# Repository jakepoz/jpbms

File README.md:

**JPBms**

JPBms is a simple BMS for solar charging and balancing a 3-cell lithium ion battery.

The key thing about it is that it uses no custom ICs, beyond a basic microcontroller. 
That is to say that it depends on no hard-to-find custom ICs that will be obsolete 3 years from now.
It implements a basic charging circuit that can charge a ~12V 3S battery from basically any input power source between
6V-24V, including if that source is a solar panel.

-------------------------------

[v1.3 Schematics](JPBms2-v1.3.pdf)

-----------------------------
- STM32L053 microcontroller
- It's just an inductor with a full set of switches on it, so you can customize it
- Simple resistive balancing
- Single layer board design for easy JLCPCB style production
  - ~$150 to order 5 from JLCPCB, way cheaper in bulk
- Low ~100uA quiescent current
- XT30 solar panel connector, JST-XH battery balance connector

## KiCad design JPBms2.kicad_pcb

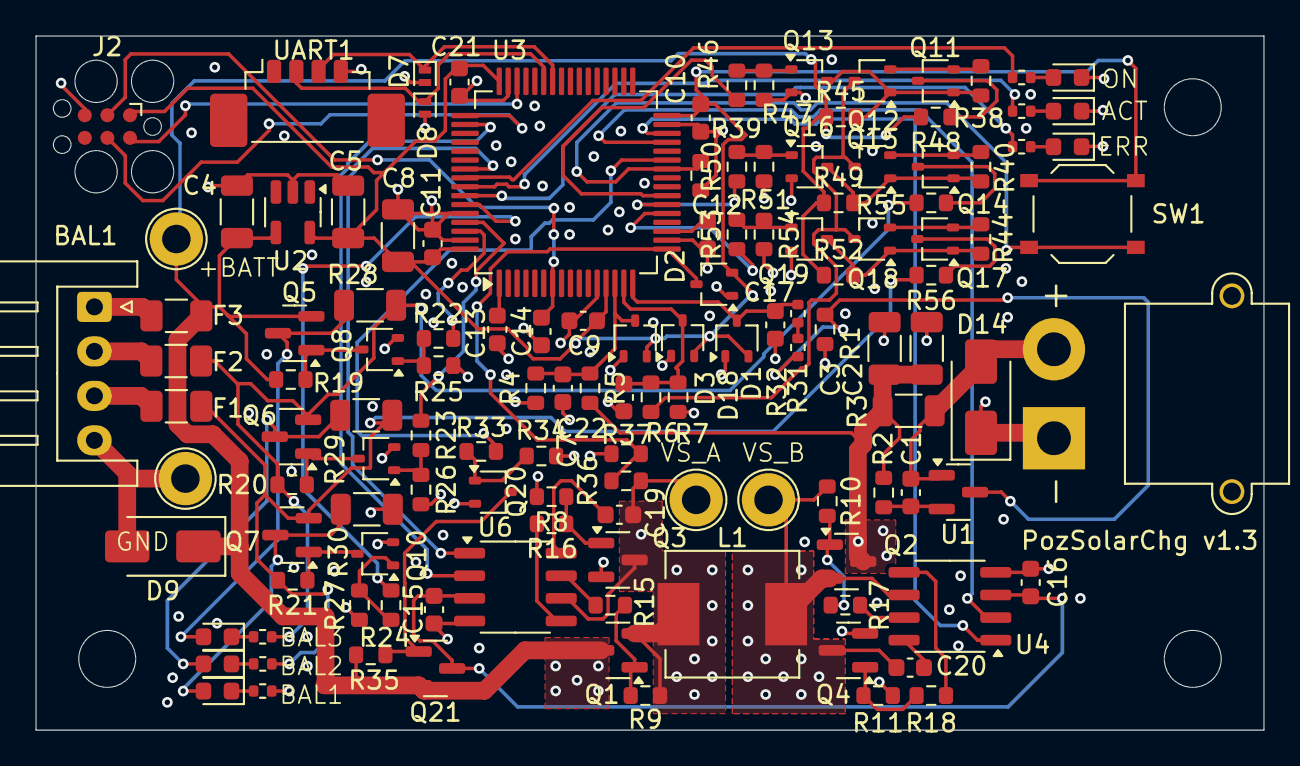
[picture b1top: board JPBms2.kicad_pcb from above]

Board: 4 copper layers, 69.0 x 39.0 mm, 132 parts (0 on the bottom side), 81 nets.

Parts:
BAL1: Conn_01x04 JST-XH; JST_XH_S4B-XH-A_1x04_P2.50mm_Horizontal_Tight
C1: 10p; C_0603_1608Metric
C2, C3, C4, C8: 10u; C_1206_3216Metric
C5: 47u; C_1206_3216Metric
C7, C9, C10, C11, C12, C13, C14, C17, C21, C22: .1u; C_0603_1608Metric
C15, C16, C19, C20: 1u; C_0603_1608Metric
D1, D2, D3, D18: BAT54SW; SOT-323_SC-70
D4: LED_G; LED_0603_1608Metric
D5, D11, D12, D13: LED_Y; LED_0603_1608Metric
D6: LED_R; LED_0603_1608Metric
D7, D8: H5VL10B; D_SOD-882
D9: SMAJ16A; D_SMA
D14: SMAJ30CA; D_SMA
F1, F2, F3: 30V 750mA; Fuse_1206_3216Metric
H1, H2, H3: MountingHole; MountingHole_3.2mm_M3
J1: XT30PW-M; AMASS_XT30PW-M_1x02_P2.50mm_Horizontal
J2: Conn_ARM_SWD_TagConnect_TC2030; Tag-Connect_TC2030-IDC-FP_2x03_P1.27mm_Vertical
L1: 47uH; L_Sunlord_MWSA0605S
Q1, Q2, Q3, Q4: AO3400A; SOT-23
Q5, Q6, Q7, Q21: AO3401A; SOT-23
Q8, Q9, Q10, Q13, Q16, Q19, Q20: 2N7002; SOT-323_SC-70
Q11, Q12, Q14, Q15, Q17, Q18: SK2301AW; SOT-323_SC-70
R1: 3k; R_0603_1608Metric
R2, R37: 4.7k; R_0603_1608Metric
R3: 0.1; R_1206_3216Metric
R4: 2k; R_0603_1608Metric
R5: 18k; R_0603_1608Metric
R6: 7500; R_0603_1608Metric
R7: 1600; R_0603_1608Metric
R8, R9, R10, R11, R19, R20, R21, R25, R26, R27, R34, R35, R38, R40, R44, R45, R47, R49, R51, R52, R54: 1M; R_0603_1608Metric
R12, R13, R14, R31, R32, R41, R42, R43: 150; R_0402_1005Metric
R15, R16, R17, R18, R48, R55, R56: 75; R_0603_1608Metric
R22, R23, R24, R33, R46, R50, R53: 1k; R_0603_1608Metric
R28, R29, R30: 100; R_1206_3216Metric
R36: 56k; R_0603_1608Metric
R39: 10M; R_0603_1608Metric
SW1: SW_Push; SW_Push_1P1T_XKB_TS-1187A
TP1: GND; TestPoint_Loop_D2.60mm_Drill1.6mm_Beaded
TP2: +BATT; TestPoint_Loop_D2.60mm_Drill1.6mm_Beaded
TP5, TP6: TestPoint; TestPoint_Loop_D2.60mm_Drill1.6mm_Beaded
U1: ZXCT1107; SOT-23
U2: ST715M25R; SOT-23-5
U3: STM32L053R8Tx; LQFP-64_10x10mm_P0.5mm
U4, U6: L6388E; SO-8_3.9x4.9mm_P1.27mm
UART1: Conn_01x04 Picoblade; Molex_PicoBlade_53398-0471_1x04-1MP_P1.25mm_Vertical

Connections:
+BATT: C4.1, D9.1 (A1), F3.2, Q1.3 (D), Q5.2 (S), Q21.2 (S), R19.1, R35.1, R45.1, R48.2, R49.1, R52.1, TP2.1, U2.4 (Vin)
/BuckBoost/DRIVER_VCC: C15.2, C16.2, Q21.3 (D), U4.3 (VCC), U6.3 (VCC)
/BuckBoost/GATE_BOT_A: Q3.1 (G), R8.1, R16.2
/BuckBoost/GATE_BOT_B: Q4.1 (G), R11.1, R18.2
/BuckBoost/GATE_TOP_A: Q1.1 (G), R9.1, R15.2
/BuckBoost/GATE_TOP_B: Q2.1 (G), R10.1, R17.2
/BuckBoost/VS_A: C19.1, L1.1, Q1.2 (S), Q3.3 (D), R9.2, R36.1, TP5.1, U6.6 (OUT)
/BuckBoost/VS_B: C20.1, L1.2, Q2.2 (S), Q4.3 (D), R10.2, TP6.1, U4.6 (OUT)
/MCU/LED_ACTIVE: R13.1, U3.57 (TIM22_CH2)
/MCU/LED_ERROR: R14.1, U3.58 (PB6)
/MCU/LED_ON: R12.1, U3.56 (TIM22_CH1)
/MCU/NRST: C14.1, J2.3 (~RESET), U3.7 (NRST)
/MCU/SWCLK: J2.4 (SWCLK), U3.49 (SYS_SWCLK)
/MCU/SWDIO: J2.2 (SWDIO), U3.46 (SYS_SWDIO)
/MCU/SWITCH: R39.2, SW1.1, U3.26 (PB0)
/MCU/USART1_RX: D8.1 (A1), U3.43 (USART1_RX), UART1.2
/MCU/USART1_TX: D7.1 (A1), U3.42 (USART1_TX), UART1.3
/Power/Vs+: C1.1, D14.2 (A2), J1.2, R3.2, U1.1 (Vs+)
CELL4V_ADC_EN: R53.1, U3.21 (PA5)
CELL8V_ADC_EN: R50.1, U3.22 (PA6)
CELL_4V: F1.2, Q7.2 (S), R21.1, R29.2, R42.1, R56.2
CELL_8V: F2.2, Q6.2 (S), R20.1, R28.2, R41.1, R55.2
COMP2_INP: D2.3 (COM), R36.2, R37.1, U3.17 (COMP2_INP)
DD_BOT_A: U3.55 (TIM2_CH2), U6.1 (LIN)
DD_BOT_B: U3.30 (TIM2_CH4), U4.1 (LIN)
DD_TOP_A: U3.50 (TIM2_CH1), U6.2 (HIN)
DD_TOP_B: U3.29 (TIM2_CH3), U4.2 (HIN)
DRIVERS_EN: R33.1, U3.27 (PB1)
GND: BAL1.4, C2.1, C3.1, C4.2, C5.2, C7.2, C8.2, C9.2, C10.2, C11.2, C12.2, C13.2, C14.2, C15.1, C16.1, C17.1, C21.2, C22.2, D1.1 (A), D2.1 (A), D3.1 (A), D4.1 (K), D5.1 (K), D6.1 (K), D7.2 (A2), D8.2 (A2), D9.2 (A2), D14.1 (A1), D18.1 (A), J1.1, J2.5 (GND), Q3.2 (S), Q4.2 (S), Q8.2 (S), Q9.2 (S), Q10.2 (S), Q13.2 (S), Q16.2 (S), Q19.2 (S), Q20.2 (S), R1.2, R4.1, R7.1, R8.2, R11.2, R25.2, R26.2, R27.2, R30.2, R34.2, R37.2, R39.1, R43.1, R47.2, R51.2, R54.2, TP1.1, U2.2 (GND), U3.12 (VSSA), U3.18 (VSS), U3.31 (VSS), U3.47 (VSS), U3.60 (BOOT0), U3.63 (VSS), U4.4 (GND), U6.4 (GND), UART1.4
NBAL_1: R24.1, U3.59 (PB7)
NBAL_2: R23.1, U3.61 (PB8)
NBAL_3: R22.1, U3.62 (PB9)
unnamed: BAL1.1, F3.1
unnamed: BAL1.2, F2.1
unnamed: BAL1.3, F1.1
unnamed: D4.2 (A), R12.2
unnamed: D5.2 (A), R13.2
unnamed: D6.2 (A), R14.2
unnamed: D11.2 (A), Q5.3 (D), R28.1
unnamed: D11.1 (K), R41.2
unnamed: D12.2 (A), Q6.3 (D), R29.1
unnamed: D12.1 (K), R42.2
unnamed: D13.2 (A), Q7.3 (D), R30.1
unnamed: D13.1 (K), R43.2
unnamed: Q5.1 (G), Q8.3 (D), R19.2
unnamed: Q6.1 (G), Q9.3 (D), R20.2
unnamed: Q8.1 (G), R22.2, R25.1
unnamed: Q9.1 (G), R23.2, R26.1
unnamed: Q7.1 (G), Q10.3 (D), R21.2
unnamed: Q10.1 (G), R24.2, R27.1
unnamed: Q11.3 (D), R48.1
unnamed: Q11.1 (G), Q12.1 (G), Q13.3 (D), R38.1, R45.2
unnamed: Q11.2 (S), Q12.2 (S), R38.2
unnamed: Q12.3 (D), Q15.3 (D), Q18.3 (D), R6.1
unnamed: Q13.1 (G), R46.2, R47.1
unnamed: Q14.3 (D), R55.1
unnamed: Q14.1 (G), Q15.1 (G), Q16.3 (D), R40.1, R49.2
unnamed: Q14.2 (S), Q15.2 (S), R40.2
unnamed: Q16.1 (G), R50.2, R51.1
unnamed: Q17.3 (D), R56.1
unnamed: Q17.1 (G), Q18.1 (G), Q19.3 (D), R44.1, R52.2
unnamed: Q17.2 (S), Q18.2 (S), R44.2
unnamed: Q19.1 (G), R53.2, R54.1
unnamed: Q20.3 (D), Q21.1 (G), R35.2
unnamed: Q20.1 (G), R33.2, R34.1
unnamed: R31.2, R32.1
unnamed: R1.1, R31.1, U1.3 (OUT)
unnamed: C1.2, R2.2, U1.2 (Vs-)
unnamed: C13.1, U3.1 (VLCD)
unnamed: R17.1, U4.7 (HVG)
unnamed: R18.1, U4.5 (LVG)
unnamed: C20.2, U4.8 (VBOOT)
unnamed: R15.1, U6.7 (HVG)
unnamed: R16.1, U6.5 (LVG)
unnamed: C19.2, U6.8 (VBOOT)
SOLAR_CURRENT_ADC: C17.2, D1.3 (COM), R32.2, U3.16 (ADC_IN2)
VBATT_ADC: C22.1, D18.3 (COM), R6.2, R7.2, U3.15 (ADC_IN1)
VBATT_ADC_EN: R46.1, U3.23 (PA7)
VDD: C5.1, C8.1, C9.1, C10.1, C11.1, C12.1, C21.1, D1.2 (K), D2.2 (K), D3.2 (K), D18.2 (K), J2.1 (VCC), SW1.2, U2.5 (Vout), U3.13 (VDDA), U3.19 (VDD), U3.32 (VDD), U3.48 (VDD_USB), U3.64 (VDD)
VSOLAR: C2.2, C3.2, Q2.3 (D), R2.1, R3.1, R5.2
VSOLAR_ADC: C7.1, D3.3 (COM), R4.2, R5.1, U3.14 (ADC_IN0)

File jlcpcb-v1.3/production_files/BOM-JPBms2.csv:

Comment,Designator,Footprint,LCSC
LED_G,D4,LED_0603_1608Metric,C12624
10u,"C2,C3,C4,C8",C_1206_3216Metric,C13585
.1u,"C10,C11,C12,C13,C14,C17,C21,C22,C7,C9",C_0603_1608Metric,C14663
AO3401A,"Q21,Q5,Q6,Q7",SOT-23,C15127
Conn_01x04 JST-XH,BAL1,JST_XH_S4B-XH-A_1x04_P2.50mm_Horizontal_Tight,C157925
1u,"C15,C16,C19,C20",C_0603_1608Metric,C15849
10p,C1,C_0603_1608Metric,C1634
100,"R28,R29,R30",R_1206_3216Metric,C17901
AO3400A,"Q1,Q2,Q3,Q4",SOT-23,C20917
1k,"R22,R23,R24,R33,R46,R50,R53",R_0603_1608Metric,C21190
LED_R,D6,LED_0603_1608Metric,C2286
LED_Y,"D11,D12,D13,D5",LED_0603_1608Metric,C2287
1M,"R10,R11,R19,R20,R21,R25,R26,R27,R34,R35,R38,R40,R44,R45,R47,R49,R51,R52,R54,R8,R9",R_0603_1608Metric,C22935
2k,R4,R_0603_1608Metric,C22975
4.7k,"R2,R37",R_0603_1608Metric,C23162
56k,R36,R_0603_1608Metric,C23206
Conn_01x04 Picoblade,UART1,Molex_PicoBlade_53398-0471_1x04-1MP_P1.25mm_Vertical,C234195
L6388E,"U4,U6",SO-8_3.9x4.9mm_P1.27mm,C23921
150,"R12,R13,R14,R31,R32,R41,R42,R43",R_0402_1005Metric,C25082
18k,R5,R_0603_1608Metric,C25810
10M,R39,R_0603_1608Metric,C26097
ST715M25R,U2,SOT-23-5,C2832805
0.1,R3,R_1206_3216Metric,C2903496
SW_Push,SW1,SW_Push_1P1T_XKB_TS-1187A,C318884
47uH,L1,L_Sunlord_MWSA0605S,C408471
3k,R1,R_0603_1608Metric,C4211
75,"R15,R16,R17,R18,R48,R55,R56",R_0603_1608Metric,C4275
XT30PW-M,J1,AMASS_XT30PW-M_1x02_P2.50mm_Horizontal,C431092
SMAJ30CA,D14,D_SMA,C5249596
7500,R6,R_0603_1608Metric,C728597
2N7002,"Q10,Q13,Q16,Q19,Q20,Q8,Q9",SOT-323_SC-70,C7420322
H5VL10B,"D7,D8",D_SOD-882,C7420372
STM32L053R8Tx,U3,LQFP-64_10x10mm_P0.5mm,C784738
BAT54SW,"D1,D18,D2,D3",SOT-323_SC-70,C78606
ZXCT1107,U1,SOT-23,C82766
1600,R7,R_0603_1608Metric,C861205
47u,C5,C_1206_3216Metric,C96123
SK2301AW,"Q11,Q12,Q14,Q15,Q17,Q18",SOT-323_SC-70,C962722
30V 750mA,"F1,F2,F3",Fuse_1206_3216Metric,C976305
+BATT,TP2,TestPoint_Loop_D2.60mm_Drill1.6mm_Beaded,
TestPoint,TP6,TestPoint_Loop_D2.60mm_Drill1.6mm_Beaded,
GND,TP1,TestPoint_Loop_D2.60mm_Drill1.6mm_Beaded,
TestPoint,TP5,TestPoint_Loop_D2.60mm_Drill1.6mm_Beaded,
SMAJ16A,D9,D_SMA,

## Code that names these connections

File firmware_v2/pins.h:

#ifndef PINS_H
#define PINS_H

#define USART1_PORT GPIOA
#define USART1_TX_PIN GPIO9
#define USART1_RX_PIN GPIO10

#define BALANCE_PORT GPIOB
#define BALANCE_1_PIN GPIO7
#define BALANCE_2_PIN GPIO8
#define BALANCE_3_PIN GPIO9

#define LED_ON_PORT GPIOB
#define LED_ON_PIN GPIO4

#define LED_ACTIVE_PORT GPIOB
#define LED_ACTIVE_PIN GPIO5

#define LED_ERROR_PORT GPIOB
#define LED_ERROR_PIN GPIO6

#define VSOLAR_ADC_PORT GPIOA
#define VSOLAR_ADC_PIN GPIO0
#define VSOLAR_ADC_CH 0

#define VBATT_ADC_PORT GPIOA
#define VBATT_ADC_PIN GPIO1
#define VBATT_ADC_CH 1

#define SOLAR_CURRENT_ADC_PORT GPIOA
#define SOLAR_CURRENT_ADC_PIN GPIO2
#define SOLAR_CURRENT_ADC_CH 2

#define TEMP_SENSOR_ADC_CH 18
#define VREFINT_ADC_CH 17

#define ADC_MULTIPLEX_PORT GPIOA
#define ADC_MULTIPLEX_CELL4V_PIN GPIO5
#define ADC_MULTIPLEX_CELL8V_PIN GPIO6
#define ADC_MULTIPLEX_VBATT_PIN GPIO7

#define SWITCH_PORT GPIOB
#define SWITCH_PIN GPIO0

#define DRIVERS_EN_PORT GPIOB
#define DRIVERS_EN_PIN GPIO1

#define BB_SW_A_PORT GPIOA
#define BB_SW_A_PIN GPIO15

#define BB_D_A_PORT GPIOB
#define BB_D_A_PIN GPIO3

#define BB_SW_B_PORT GPIOB
#define BB_SW_B_PIN GPIO10

#define BB_D_B_PORT GPIOB
#define BB_D_B_PIN GPIO11


#endif

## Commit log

2024-04-18 Many stages done
2024-04-18 prefs
2024-04-18 removing old
2024-04-18 Some part selections
2024-04-19 Text
2024-04-20 Connect adc
2024-04-21 Starting to do layout
2024-04-24 Adding simple balance circuits
2024-04-26 Footprint
2024-04-26 Smaller diodes, more work
2024-04-26 Some more placement
2024-04-26 More layout adust
2024-04-26 Smallfixups
2024-04-27 Routing more
2024-04-27 Routing
2024-05-03 Layout done
2024-05-03 bom pt1
2024-05-06 Assigning PNs
2024-05-06 slight changes
2024-05-06 sent to jlcpcb
2024-05-14 Schematics updated P mosfets
2024-05-14 New design and layout
2024-05-15 Finishing layout
2024-05-15 Better balance resistors, fixes
2024-05-15 N fets
2024-05-15 V1.1 spin
2024-05-15 V1.1 gerbers made
2024-05-21 Adding a few calculations
2024-05-21 Notes for v2
2024-05-22 Adding some notes
2024-05-22 Adding notes, committing firmware to repo
2024-05-22 Added plugged in detection
2024-05-22 Uart working
2024-05-22 More notes
2024-05-22 Adding a few notes, adding detection on solar and uart plugs
2024-05-22 Adding flow chart to main.c Adding leds on balancers
2024-05-23 TIM2 tests
2024-05-23 Starting to write state machine code
2024-05-23 Organizing project into multiple files
2024-05-23 Writing up more state stuff for balancing. Next up is probably a state change and state timing mechanism
2024-05-23 Writing up a more sensical state machine
2024-05-23 Add some TODOs
2024-05-24 Fixing up state machine, inductor circuit working better
2024-05-24 Adding notes
2024-05-25 Save power with usart, add oversampling support when balancing to get better reading, add notes on pcb
2024-05-26 Adding notes, solder jumpers for picking polarity of dc plugs
2024-05-26 notes
2024-05-28 Adding XT30 solar connector
2024-05-28 Adding switch, moving current sense
2024-05-28 Starting draft of ADC multiplexer
2024-05-28 Adding ADC multiplexer, protection diodes
2024-05-28 Moving balance resistors to make more sense
2024-05-29 Adding new ST driver, protecting uart input
2024-05-29 Basic charging code, stupid power connector was reversed
2024-05-29 Checking out more functionality in the code
2024-05-30 Code to properly switch to HSI16 clock during buck boosting
2024-05-30 Code cleanup, notes on gate oscillations
2024-06-04 Starting work to trigger ADC on TIM2
2024-06-04 Fix for adc trigger, but it's still not going continuously
2024-06-04 Yay, working triggered conversions with ADC
2024-06-04 Totally broken MPPT
2024-06-05 Basic MPPT working, going back out of buckboost mode works too
2024-06-05 Running apb2 at 16mhz now
2024-06-06 More reliable MPPT tracking
2024-06-07 Taking notes, doing some final adjustments to RC filter values
2024-06-07 Starting to read current values and convert them
2024-06-07 L6388E mosfet drivers
    Allow to enable/disable drivers
    voltage dividers picked out
2024-06-07 New schematic done
2024-06-08 A couple of part selections
2024-06-09 Layout
2024-06-09 Decent pass
2024-06-09 Routing pt1
2024-06-10 More routing
2024-06-10 94 unrouted
2024-06-10 35 left
2024-06-10 17 left
2024-06-10 It is routed
2024-06-10 Fine tuning routing
2024-06-10 Better thermal pads
2024-06-10 Starting cleanup
2024-06-10 Some label cleanup, but it's a packed board
2024-06-10 V1.2 production
2024-06-19 Adding button support, changing the sample stuff to match the new schematics, new pin defintions, first few v1.3 ideas
2024-06-20 Wohoo, we actually have super precise cell voltage readings now down to 1 LSB
2024-06-20 Labeling balance leds properly
2024-06-20 Cleanup balancing logic
2024-06-20 enterring charge state
2024-06-20 Voltage control MPPT works a lot better I would say
2024-06-25 Making notes, voltage controlled MPPT now works better, more efficient low side during charge phase
2024-06-28 Making some notes to increase accuracy, perhaps with vref
2024-06-29 More accurate VBATT resistors, recalibrated vbatt off of vrefint, getting 0.5% accurate readings now
2024-07-04 Much faster adc_isr now
2024-07-06 Board 1.3 ready -> fixed comparator inputs, balance LEDs, and TVS diode for battery disconnect protection
2024-07-08 v1.3 JLCPCB production
2024-07-08 Adding an LCSC code, should have been obvious though
2024-07-17 Finally reading battery within full precision!
2024-07-20 V1.3 getting ready to show some friends
